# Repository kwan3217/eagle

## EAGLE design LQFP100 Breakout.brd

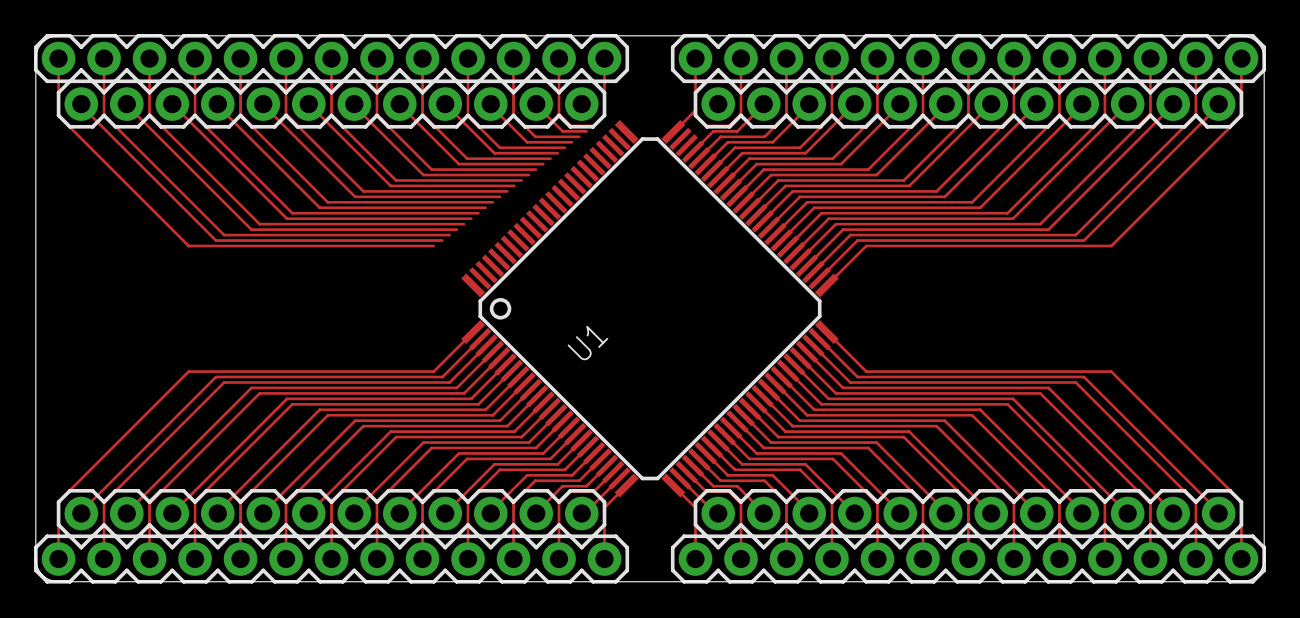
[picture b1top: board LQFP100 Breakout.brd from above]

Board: 2 copper layers, 68.6 x 30.5 mm, 9 parts (0 on the bottom side), 100 nets.

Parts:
JP1, JP2, JP3, JP4: M13; 1X13
JP5, JP6, JP7, JP8: M12PTH; 1X12
U1: LPC2368; LQFP100

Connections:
unnamed: JP1.1, U1.1
unnamed: JP5.1, U1.2
unnamed: JP1.2, U1.3
unnamed: JP5.2, U1.4
unnamed: JP1.3, U1.5
unnamed: JP5.3, U1.6
unnamed: JP1.4, U1.7
unnamed: JP5.4, U1.8
unnamed: JP1.5, U1.9
unnamed: JP5.5, U1.10
unnamed: JP1.6, U1.11
unnamed: JP5.6, U1.12
unnamed: JP1.7, U1.13
unnamed: JP5.7, U1.14
unnamed: JP1.8, U1.15
unnamed: JP5.8, U1.16
unnamed: JP1.9, U1.17
unnamed: JP5.9, U1.18
unnamed: JP1.10, U1.19
unnamed: JP5.10, U1.20
unnamed: JP1.11, U1.21
unnamed: JP5.11, U1.22
unnamed: JP1.12, U1.23
unnamed: JP5.12, U1.24
unnamed: JP1.13, U1.25
unnamed: JP2.13, U1.26
unnamed: JP6.12, U1.27
unnamed: JP2.12, U1.28
unnamed: JP6.11, U1.29
unnamed: JP2.11, U1.30
unnamed: JP6.10, U1.31
unnamed: JP2.10, U1.32
unnamed: JP6.9, U1.33
unnamed: JP2.9, U1.34
unnamed: JP6.8, U1.35
unnamed: JP2.8, U1.36
unnamed: JP6.7, U1.37
unnamed: JP2.7, U1.38
unnamed: JP6.6, U1.39
unnamed: JP2.6, U1.40
unnamed: JP6.5, U1.41
unnamed: JP2.5, U1.42
unnamed: JP6.4, U1.43
unnamed: JP2.4, U1.44
unnamed: JP6.3, U1.45
unnamed: JP2.3, U1.46
unnamed: JP6.2, U1.47
unnamed: JP2.2, U1.48
unnamed: JP6.1, U1.49
unnamed: JP2.1, U1.50
unnamed: JP4.13, U1.51
unnamed: JP7.12, U1.52
unnamed: JP4.12, U1.53
unnamed: JP7.11, U1.54
unnamed: JP4.11, U1.55
unnamed: JP7.10, U1.56
unnamed: JP4.10, U1.57
unnamed: JP7.9, U1.58
unnamed: JP4.9, U1.59
unnamed: JP7.8, U1.60
unnamed: JP4.8, U1.61
unnamed: JP7.7, U1.62
unnamed: JP4.7, U1.63
unnamed: JP7.6, U1.64
unnamed: JP4.6, U1.65
unnamed: JP7.5, U1.66
unnamed: JP4.5, U1.67
unnamed: JP7.4, U1.68
unnamed: JP4.4, U1.69
unnamed: JP7.3, U1.70
unnamed: JP4.3, U1.71
unnamed: JP7.2, U1.72
unnamed: JP4.2, U1.100
unnamed: JP7.1, U1.99
unnamed: JP4.1, U1.98
unnamed: JP3.13, U1.83
unnamed: JP8.12, U1.96
unnamed: JP3.12, U1.95
unnamed: JP8.11, U1.94
unnamed: JP3.11, U1.93
unnamed: JP8.10, U1.92
unnamed: JP3.10, U1.73
unnamed: JP8.9, U1.74
unnamed: JP3.9, U1.75
unnamed: JP8.8, U1.76
unnamed: JP3.8, U1.77
unnamed: JP8.7, U1.78
unnamed: JP3.7, U1.79
unnamed: JP8.6, U1.80
unnamed: JP3.6, U1.81
unnamed: JP8.5, U1.82
unnamed: JP3.5, U1.97
unnamed: JP8.4, U1.84
unnamed: JP3.4, U1.85
unnamed: JP8.3, U1.86
unnamed: JP3.3, U1.87
unnamed: JP8.2, U1.88
unnamed: JP3.2, U1.89
unnamed: JP8.1, U1.90
unnamed: JP3.1, U1.91

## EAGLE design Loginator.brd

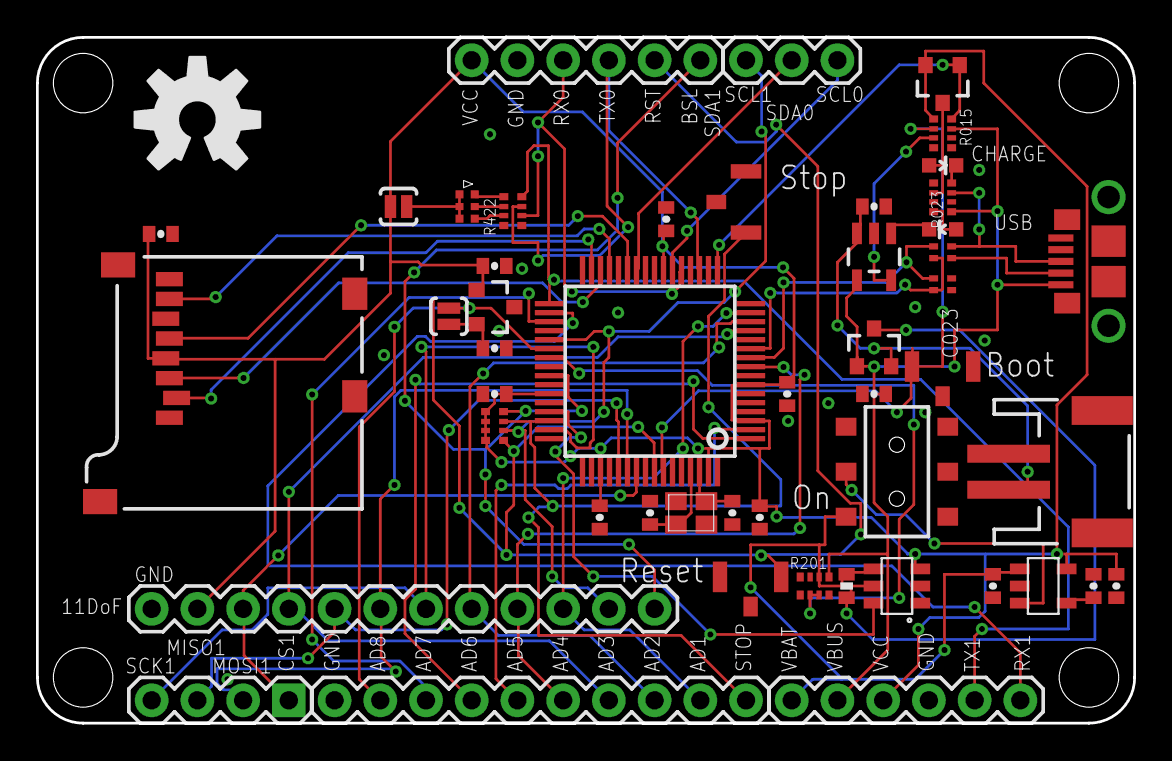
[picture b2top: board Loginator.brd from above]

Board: 2 copper layers, 61.0 x 38.1 mm, 55 parts (1 on the bottom side), 54 nets.

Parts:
C023: 22pF; CKCM25
C201, C301, C302, C438: 4.7uF; 0402-CAP
C203, C407, C423, C432, C443, C451, C463, C701: 100nF; 0402-CAP
C204: 1uF; 0402-CAP
C461, C462: 18pF; 0402-CAP
D050: YELLOW; LED-0603
D301: BLUE; LED-0603
D302: DCC; SOT-23-3
D401: SMLP36
J001: USB_MICROB_JSTGCT; USB_MICROB_3075
J002: M01PTH; 1X03
J301: JST 2mm; JST-2-SMD
J401, J404: M06; 1X06
J402: M04; 1X04
J403: M10; 1X10
J406: 11DoF; 1X12
JP1, JP2, JP3, JP4: STAND-OFF
Q050: PMOS; SOT23-3
R015, R401: 10k; CRA04
R023: 33; CRA02
R053: 1.5k; CRA04
R201: 100k; CRA04
R203: 0.047; 0402-RES
R422: 150; CRA04
S010, S420, S457: SPST; B3U-1100P
S201: AYZ0202
S401, S438: SOLDERJUMPERNO; SJ_2S-NO
U201: 5319; SOT-23-5
U202: 4173; SOT-23-6
U301: 73831; SOT23-5
U401: LPC2148; SQFP-S-10X10-64
U402: 1525; SOT-23-3
U701: MICROSD-SOCKET; MICROSD-SOCKET-PP
U$1: KWAN_CIRCLE
U$2: OSHW-LOGO-L
Y401: 12MHz; CRYSTAL_SMD_2MM_2_5MM

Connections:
AD1: J403.9, J406.3, U401.15
AD2: J403.8, J406.5, U401.14
AD3: J403.7, J406.9, U401.13
AD4: J403.6, J406.4, U401.9
AD5: J403.5, U401.2
AD6: J403.4, U401.1
AD7: J403.3, U401.35
ADREF+: C438.1, S438.1, U402.2
ADREF-: J403.2, S438.2, U401.38
BATLVL: R201.2, R201.3, U401.39
CONN_D+: J001.3, R023.2, R053.7
CONN_D-: J001.2, R023.1
CS0: U401.31, U701.2
CS1: J402.1, J406.10, U401.55
CURRENT: U202.6, U401.45
DB: D401.3, R422.6
DG: D401.5, R422.7
DR: D401.1, R422.5
EN: S201.2, U201.3
GND: C023.3, C023.4, C201.2, C203.2, C204.2, C301.2, C302.2, C407.2, C423.2, C432.2, C438.2, C443.2, C451.2, C461.1, C462.1, C463.2, C701.2, J001.5, J001.P$1, J001.P$2, J001.P$3, J001.P$4, J001.P$8, J001.P$10, J301.1, J401.5, J403.1, J404.4, J406.12, R015.6, R053.1, R201.1, R201.4, R201.7, R201.8, S010.P$2, S010.P$3, S201.3, S420.P$1, S420.P$3, S457.P$1, S457.P$3, U201.2, U202.1, U202.2, U301.2, U401.6, U401.18, U401.25, U401.42, U401.50, U401.59, U402.3, U701.6, U701.CD2, U701.GND1, U701.GND3, Y401.2, Y401.4
MISO0: U401.29, U701.7
MISO1: J402.3, J406.8, U401.53
MOSI0: U401.30, U701.3
MOSI1: J402.2, J406.7, U401.54
unnamed: D301.A, R053.4
unnamed: R015.3, U301.5
unnamed: D301.C, U301.1
unnamed: D050.A, Q050.3, R053.2
unnamed: D050.C, R053.8
unnamed: C203.1, U201.4
RGB_Q: D401.2, D401.4, D401.6, S401.1
RST: J401.2, R401.5, S457.P$2, U401.57
RX0/PWMG: J401.4, R422.2, U401.21
RX1: J404.6, U401.34
SCK0: U401.27, U701.5
SCK1: J402.4, J406.6, U401.47
SCL0: J002.1, U401.22
SCL1: J002.3, J406.2, R401.6, U401.37
SDA0: J002.2, U401.26
SDA1/BSL: J401.1, J406.1, R401.8, U401.41
STOP: J403.10, R401.7, S420.P$2, U401.46
TX0/PWMB: J401.3, R422.3, U401.19
TX1/PWMR: J404.5, R422.4, U401.33
USBD+: C023.1, R023.3, U401.10
USBD-: C023.2, R023.4, U401.11
USB_ON: R015.2, S010.P$1, U401.58
USB_SOFTCONNECT: Q050.1, R015.8, U401.17
VBUS: C302.1, D302.1, J001.1, J404.2, R015.7, R053.5, R201.5, U301.4
VCC: C201.1, C407.1, C423.1, C432.1, C443.1, C451.1, C463.1, C701.1, J401.6, J404.3, J406.11, Q050.2, R015.1, R401.1, R401.2, R401.3, R401.4, S401.2, U201.5, U202.3, U401.3, U401.7, U401.23, U401.43, U401.49, U401.51, U401.63, U402.1, U701.4
VIN+: D302.3, R203.1, U202.5
VIN-: C204.1, J404.1, R201.6, R203.2, S201.1, U201.1, U202.4
VLIPO: C301.1, D302.2, J301.2, U301.3
XTAL1: C462.2, U401.62, Y401.1
XTAL2: C461.2, U401.61, Y401.3

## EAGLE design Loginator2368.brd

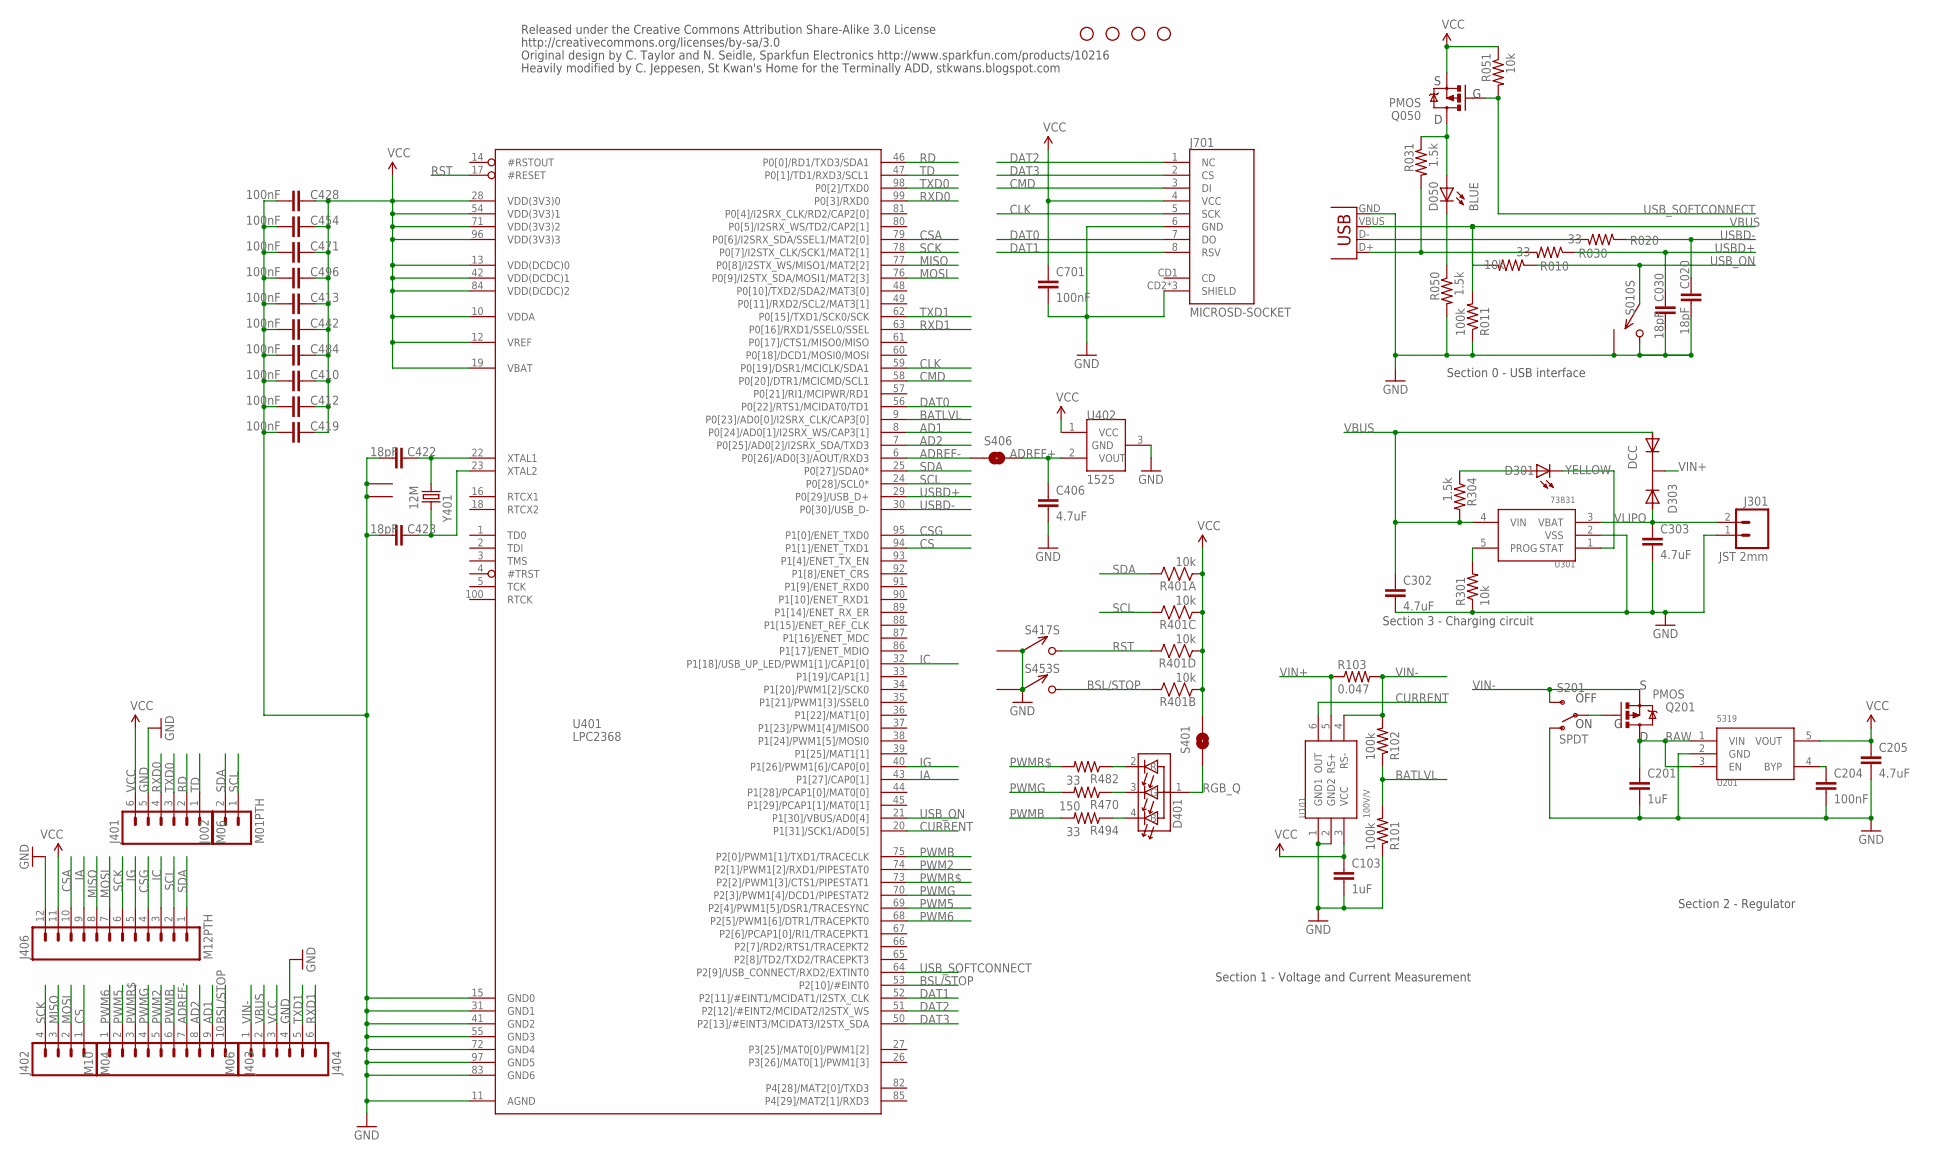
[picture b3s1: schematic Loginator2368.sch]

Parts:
C020, C030, C422, C423: 18pF; 0402-CAP; DIGIKEY 445-1238-1-ND
C103, C201: 1uF; 0402-CAP; DIGIKEY 445-1415-1-ND
C204, C410, C412, C413, C419, C428, C442, C454, C471, C484, C496, C701: 100nF; 0402-CAP; DIGIKEY 445-1268-1-ND
C205, C302, C303, C406: 4.7uF; 0402-CAP; DIGIKEY 445-7395-1-ND
D050: BLUE; LED-0603; DIGIKEY 754-1434-1-ND
D301: YELLOW; LED-0603; DIGIKEY 754-1354-1-ND
D303: DCC; SOT-23-3; DIGIKEY 568-6500-1-ND
D401: RGB; HSMF-C118; DIGIKEY 516-1778-1-ND
J001: USBSMD; USB-MINIB; DIGIKEY 670-1190-1-ND
J002: M01PTH; 1X02; DIGIKEY $NOPART
J301: JST 2mm; JST-2-SMD; DIGIKEY 455-1749-1-ND
J401, J404: M06; 1X06; DIGIKEY $NOPART
J402: M04; 1X04; DIGIKEY $NOPART
J403: M10; 1X10; DIGIKEY $NOPART
J406: M12PTH; 1X12; DIGIKEY $NOPART
J701: MICROSD-SOCKET; MICROSD-SOCKET-PP; DIGIKEY 101-00581-59-1-ND
JP1, JP2, JP3, JP4: STAND-OFF; DIGIKEY $NOPART
Q050, Q201: PMOS; SOT23-3; DIGIKEY NTR1P02T1GOSCT-ND
R010, R051, R301: 10k; 0402-RES; DIGIKEY P10.0KLCT-ND
R011, R101, R102: 100k; 0402-RES; DIGIKEY P100KLCT-ND
R020, R030, R482, R494: 33; 0402-RES; DIGIKEY P33.0LCT-ND
R031, R050, R304: 1.5k; 0402-RES; DIGIKEY P1.50KLCT-ND
R103: 0.047; 0402-RES; DIGIKEY P.047ATCT-ND
R401: 10k; CRA04; DIGIKEY CRA4S810KCT-ND
R470: 150; 0402-RES; DIGIKEY P150LCT-ND
S010, S417, S453: SPST; B3U-1100P; DIGIKEY SW1021CT-ND
S201: SPDT; AYZ0202; DIGIKEY 401-2013-1-ND
S401, S406: SOLDERJUMPERNO; SJ_2S-NO; DIGIKEY $NOPART
U101: 100V/V; SOT-23-6; DIGIKEY MAX4173HEUT+TCT-ND
U201: 5319; SOT-23-5; DIGIKEY 576-1910-1-ND
U301: 73831; SOT-23-5; DIGIKEY MCP73831T-2ACI/OTCT-ND
U401: LPC2368; LQFP100; DIGIKEY 568-3997-ND
U402: 1525; SOT-23-3; DIGIKEY MCP1525T-I/TTCT-ND
Y401: 12M; CRYSTAL_SMD; DIGIKEY 887-1316-1-ND

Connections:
AD1: J403.9, U401.8 (P0[24]/AD0[1]/I2SRX_WS/CAP3[1])
AD2: J403.8, U401.7 (P0[25]/AD0[2]/I2SRX_SDA/TXD3)
ADREF+: C406.1, S406.1, U402.2 (VOUT)
ADREF-: J403.7, S406.2, U401.6 (P0[26]/AD0[3]/AOUT/RXD3)
BATLVL: R101.2, R102.1, U401.9 (P0[23]/AD0[0]/I2SRX_CLK/CAP3[0])
BSL/STOP: J403.10, R401.7 (2), S453.P$2 (2), U401.53 (P2[10]/#EINT0)
CLK: J701.5 (SCK), U401.59 (P0[19]/DSR1/MCICLK/SDA1)
CMD: J701.3 (DI), U401.58 (P0[20]/DTR1/MCICMD/SCL1)
CONN_D+: J001.D+, R030.2, R031.2
CONN_D-: J001.D-, R020.2
CS: J402.1, U401.94 (P1[1]/ENET_TXD1)
CSA: J406.10, U401.79 (P0[6]/I2SRX_SDA/SSEL1/MAT2[0])
CSG: J406.4, U401.95 (P1[0]/ENET_TXD0)
CURRENT: U101.6 (OUT), U401.20 (P1[31]/SCK1/AD0[5])
DAT0: J701.7 (DO), U401.56 (P0[22]/RTS1/MCIDAT0/TD1)
DAT1: J701.8 (RSV), U401.52 (P2[11]/#EINT1/MCIDAT1/I2STX_CLK)
DAT2: J701.1 (NC), U401.51 (P2[12]/#EINT2/MCIDAT2/I2STX_WS)
DAT3: J701.2 (CS), U401.50 (P2[13]/#EINT3/MCIDAT3/I2STX_SDA)
DB: D401.4 (B), R494.1
DG: D401.2 (R), R482.1
DR: D401.3 (G), R470.1
GND: C020.2, C030.2, C103.2, C201.2, C204.2, C205.2, C302.2, C303.2, C406.2, C410.2, C412.2, C413.2, C419.2, C422.1, C423.1, C428.2, C442.2, C454.2, C471.2, C484.2, C496.2, C701.2, J001.GND, J301.1, J401.5, J404.4, J406.12, J701.6 (GND), J701.CD2 (SHIELD), J701.GND1 (SHIELD), J701.GND3 (SHIELD), R011.1, R050.2, R101.1, R301.1, S010.P$2 (2), S010.P$3 (1), S201.1 (O), S417.P$1 (1), S417.P$3 (1), S453.P$1 (1), S453.P$3 (1), U101.1 (GND1), U101.2 (GND2), U201.2 (GND), U301.2 (VSS), U401.11 (AGND), U401.15 (GND0), U401.31 (GND1), U401.41 (GND2), U401.55 (GND3), U401.72 (GND4), U401.83 (GND6), U401.97 (GND5), U402.3 (GND), Y401.2 (1), Y401.4 (1)
IA: J406.9, U401.43 (P1[27]/CAP0[1])
IC: J406.3, U401.32 (P1[18]/USB_UP_LED/PWM1[1]/CAP1[0])
IG: J406.5, U401.40 (P1[26]/PWM1[6]/CAP0[0])
MISO: J402.3, J406.8, U401.77 (P0[8]/I2STX_WS/MISO1/MAT2[2])
MOSI: J402.2, J406.7, U401.76 (P0[9]/I2STX_SDA/MOSI1/MAT2[3])
unnamed: D301.A, R304.1
unnamed: R301.2, U301.5 (PROG)
unnamed: D301.C, U301.1 (STAT)
unnamed: D050.A, Q050.3 (D), R031.1
unnamed: D050.C, R050.1
unnamed: Q201.1 (G), S201.2
unnamed: C204.1, U201.4 (BYP)
PWM2: J403.5, U401.74 (P2[1]/PWM1[2]/RXD1/PIPESTAT0)
PWM5: J403.2, U401.69 (P2[4]/PWM1[5]/DSR1/TRACESYNC)
PWM6: J403.1, U401.68 (P2[5]/PWM1[6]/DTR1/TRACEPKT0)
PWMB: J403.6, R494.2, U401.75 (P2[0]/PWM1[1]/TXD1/TRACECLK)
PWMG: J403.4, R470.2, U401.70 (P2[3]/PWM1[4]/DCD1/PIPESTAT2)
PWMR$: J403.3, R482.2, U401.73 (P2[2]/PWM1[3]/CTS1/PIPESTAT1)
RAW: C201.1, Q201.3 (D), U201.1 (VIN), U201.3 (EN)
RD: J401.2, U401.46 (P0[0]/RD1/TXD3/SDA1)
RGB_Q: D401.1 (A), S401.1
RST: R401.5 (2), S417.P$2 (2), U401.17 (#RESET)
RXD0: J401.4, U401.99 (P0[3]/RXD0)
RXD1: J404.6, U401.63 (P0[16]/RXD1/SSEL0/SSEL)
SCK: J402.4, J406.6, U401.78 (P0[7]/I2STX_CLK/SCK1/MAT2[1])
SCL: J002.1, J406.2, R401.6 (2), U401.24 (P0[28]/SCL0*)
SDA: J002.2, J406.1, R401.8 (2), U401.25 (P0[27]/SDA0*)
TD: J401.1, U401.47 (P0[1]/TD1/RXD3/SCL1)
TXD0: J401.3, U401.98 (P0[2]/TXD0)
TXD1: J404.5, U401.62 (P0[15]/TXD1/SCK0/SCK)
USBD+: C030.1, R030.1, U401.29 (P0[29]/USB_D+)
USBD-: C020.1, R020.1, U401.30 (P0[30]/USB_D-)
USB_ON: R010.1, S010.P$1 (1), U401.21 (P1[30]/VBUS/AD0[4])
USB_SOFTCONNECT: Q050.1 (G), R051.2, U401.64 (P2[9]/USB_CONNECT/RXD2/EXTINT0)
VBUS: C302.1, D303.1 (A1), J001.VBUS, J404.2, R010.2, R011.2, R304.2, U301.4 (VIN)
VCC: C103.1, C205.1, C410.1, C412.1, C413.1, C419.1, C428.1, C442.1, C454.1, C471.1, C484.1, C496.1, C701.1, J401.6, J404.3, J406.11, J701.4 (VCC), Q050.2 (S), R051.1, R401.1, R401.2 (1), R401.3 (1), R401.4 (1), S401.2, U101.3 (VCC), U201.5 (VOUT), U401.10 (VDDA), U401.12 (VREF), U401.13 (VDD(DCDC)0), U401.19 (VBAT), U401.28 (VDD(3V3)0), U401.42 (VDD(DCDC)1), U401.54 (VDD(3V3)1), U401.71 (VDD(3V3)2), U401.84 (VDD(DCDC)2), U401.96 (VDD(3V3)3), U402.1 (VCC)
VIN+: D303.3 (K), R103.1, U101.5 (RS+)
VIN-: J404.1, Q201.2 (S), R102.2, R103.2, S201.3 (S), U101.4 (RS-)
VLIPO: C303.1, D303.2 (A2), J301.2, U301.3 (VBAT)
XTAL1: C422.2, U401.22 (XTAL1), Y401.3 (2)
XTAL2: C423.2, U401.23 (XTAL2), Y401.1

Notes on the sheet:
Section 2 - Regulator
Section 3 - Charging circuit
Section 0 - USB interface
Released under the Creative Commons Attribution Share-Alike 3.0 License
http://creativecommons.org/licenses/by-sa/3.0
Original design by C. Taylor and N. Seidle, Sparkfun Electronics http://www.sparkfun.com/products/10216
Heavily modified by C. Jeppesen, St Kwan's Home for the Terminally ADD, stkwans.blogspot.com
Section 1 - Voltage and Current Measurement
OFF

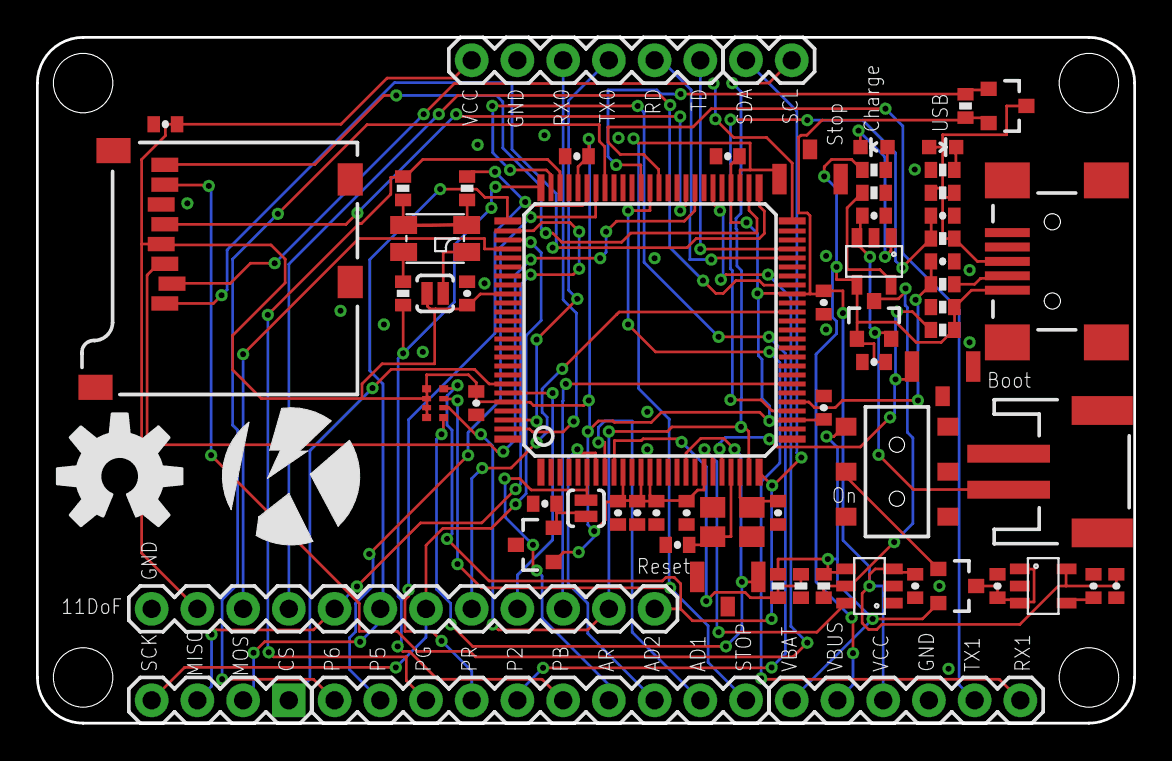
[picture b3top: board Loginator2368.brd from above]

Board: 2 copper layers, 61.0 x 38.1 mm, 71 parts (0 on the bottom side), 63 nets.

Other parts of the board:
U$1: KWAN_CIRCLE
U$2: OSHW-LOGO-L

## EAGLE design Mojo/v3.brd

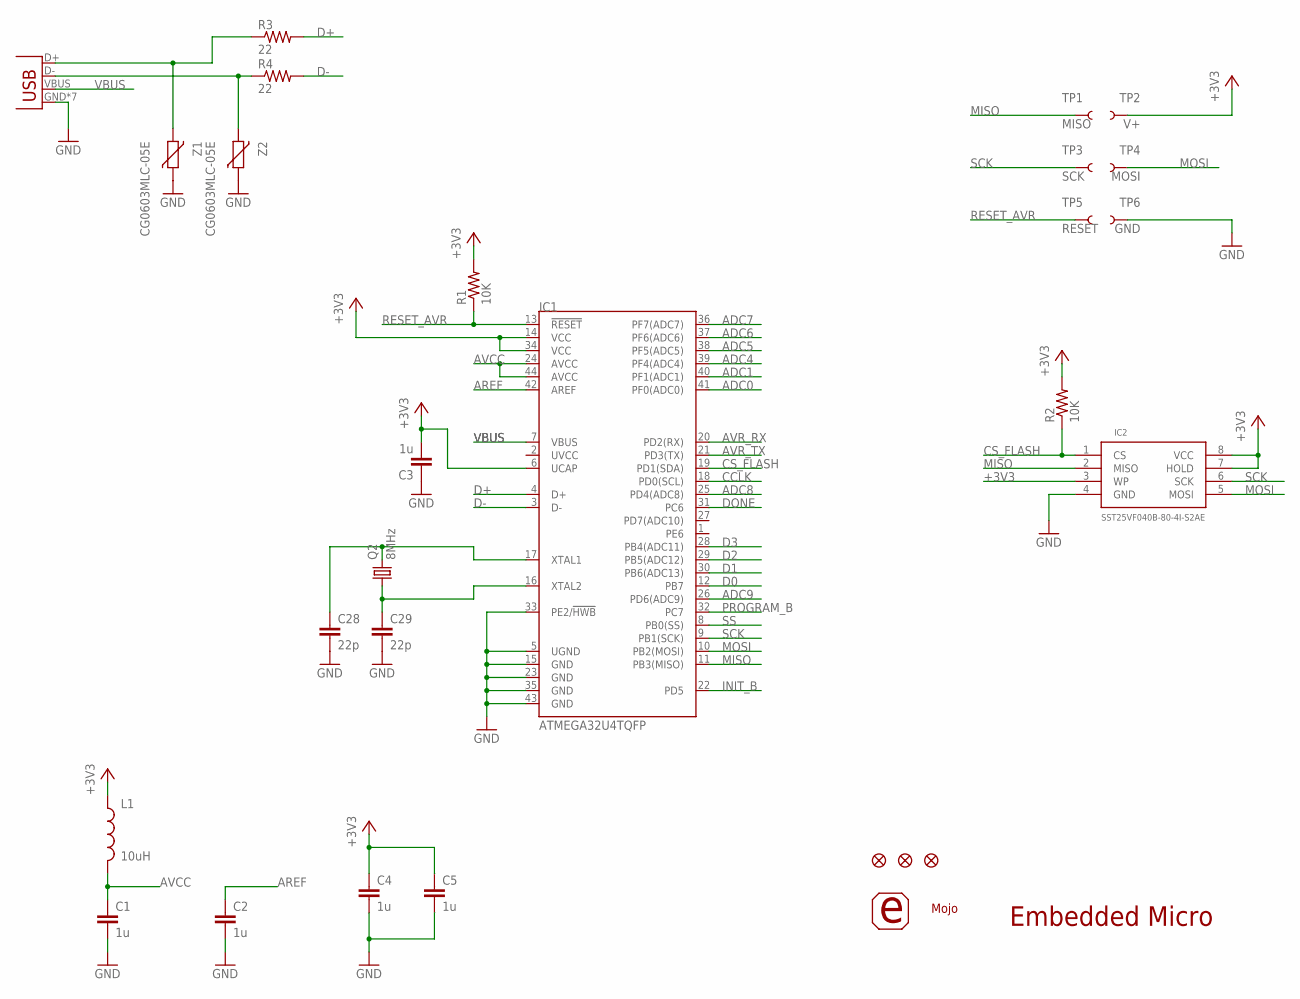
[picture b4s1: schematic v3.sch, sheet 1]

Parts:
C1, C2, C3, C4, C5: 1u; C0603K
C28, C29: 22p; C0603K
IC1: ATMEGA32U4TQFP; SPARKFUN-DIGITALIC_TQFP44
IC2: SST25VF040B-80-4I-S2AE; SO08-EIAJ
JP3, JP4, JP5: FIDUCIAL1X2; FIDUCIAL-1X2
L1: 10uH; 0603
Q2: 8MHz; ABM2
R1, R2: 10K; R0603
R3, R4: 22; R0603
TP1: MISO; PAD.03X.05
TP2: V+; PAD.03X.05
TP3: SCK; PAD.03X.05
TP4: MOSI; PAD.03X.05
TP5: RESET; PAD.03X.05
TP6: GND; PAD.03X.05
U$1: LOGO(SMALL)SMALL; LOGO
U$2: MOJO_LOGOV3; MOJO_LOGO_V3
X1: USB-MICROB
Z1, Z2: CG0603MLC-05E; CT/CN0603

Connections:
+3V3: C3.2, C4.1, C5.1, IC1.6 (UCAP), IC1.14 (VCC), IC1.34 (VCC), IC2.3 (WP), IC2.7 (HOLD), IC2.8 (VCC), L1.1, R1.2, R2.2, TP2.P$1; also elsewhere on the board
ADC0: IC1.41 (PF0(ADC0)); also elsewhere on the board
ADC1: IC1.40 (PF1(ADC1)); also elsewhere on the board
ADC4: IC1.39 (PF4(ADC4)); also elsewhere on the board
ADC5: IC1.38 (PF5(ADC5)); also elsewhere on the board
ADC6: IC1.37 (PF6(ADC6)); also elsewhere on the board
ADC7: IC1.36 (PF7(ADC7)); also elsewhere on the board
ADC8: IC1.25 (PD4(ADC8)); also elsewhere on the board
ADC9: IC1.26 (PD6(ADC9)); also elsewhere on the board
AREF: C2.1, IC1.42 (AREF); also elsewhere on the board
AVCC: C1.1, IC1.24 (AVCC), IC1.44 (AVCC), L1.2
AVR_RX: IC1.20 (PD2(RX)); also elsewhere on the board
AVR_TX: IC1.21 (PD3(TX)); also elsewhere on the board
CCLK: IC1.18 (PD0(SCL)); also elsewhere on the board
CS_FLASH: IC1.19 (PD1(SDA)), IC2.1 (CS), R2.1
D0: IC1.12 (PB7); also elsewhere on the board
D1: IC1.30 (PB6(ADC13)); also elsewhere on the board
D2: IC1.29 (PB5(ADC12)); also elsewhere on the board
D3: IC1.28 (PB4(ADC11)); also elsewhere on the board
D+: IC1.4 (D+), R3.2
D-: IC1.3 (D-), R4.2
DONE: IC1.31 (PC6); also elsewhere on the board
GND: C1.2, C2.2, C3.1, C4.2, C5.2, C28.2, C29.2, IC1.5 (UGND), IC1.15 (GND), IC1.23 (GND), IC1.33 (PE2/!HWB), IC1.35 (GND), IC1.43 (GND), IC2.4 (GND), TP6.P$1, X1.GND, X1.P1 (GND), X1.P2 (GND), X1.P3 (GND), X1.P4 (GND), X1.P5 (GND), X1.P6 (GND), Z1.1, Z2.1; also elsewhere on the board
INIT_B: IC1.22 (PD5); also elsewhere on the board
MISO: IC1.11 (PB3(MISO)), IC2.2 (MISO), TP1.P$1; also elsewhere on the board
MOSI: IC1.10 (PB2(MOSI)), IC2.5 (MOSI), TP4.P$1; also elsewhere on the board
unnamed: R3.1, X1.D+, Z1.2
unnamed: R4.1, X1.D-, Z2.2
unnamed: C28.1, IC1.17 (XTAL1), Q2.P$2 (2)
unnamed: C29.1, IC1.16 (XTAL2), Q2.P$1 (1)
PROGRAM_B: IC1.32 (PC7); also elsewhere on the board
RESET_AVR: IC1.13 (!RESET), R1.1, TP5.P$1
SCK: IC1.9 (PB1(SCK)), IC2.6 (SCK), TP3.P$1; also elsewhere on the board
SS: IC1.8 (PB0(SS)); also elsewhere on the board
VBUS: IC1.7 (VBUS), X1.VBUS; also elsewhere on the board

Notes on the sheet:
Embedded Micro

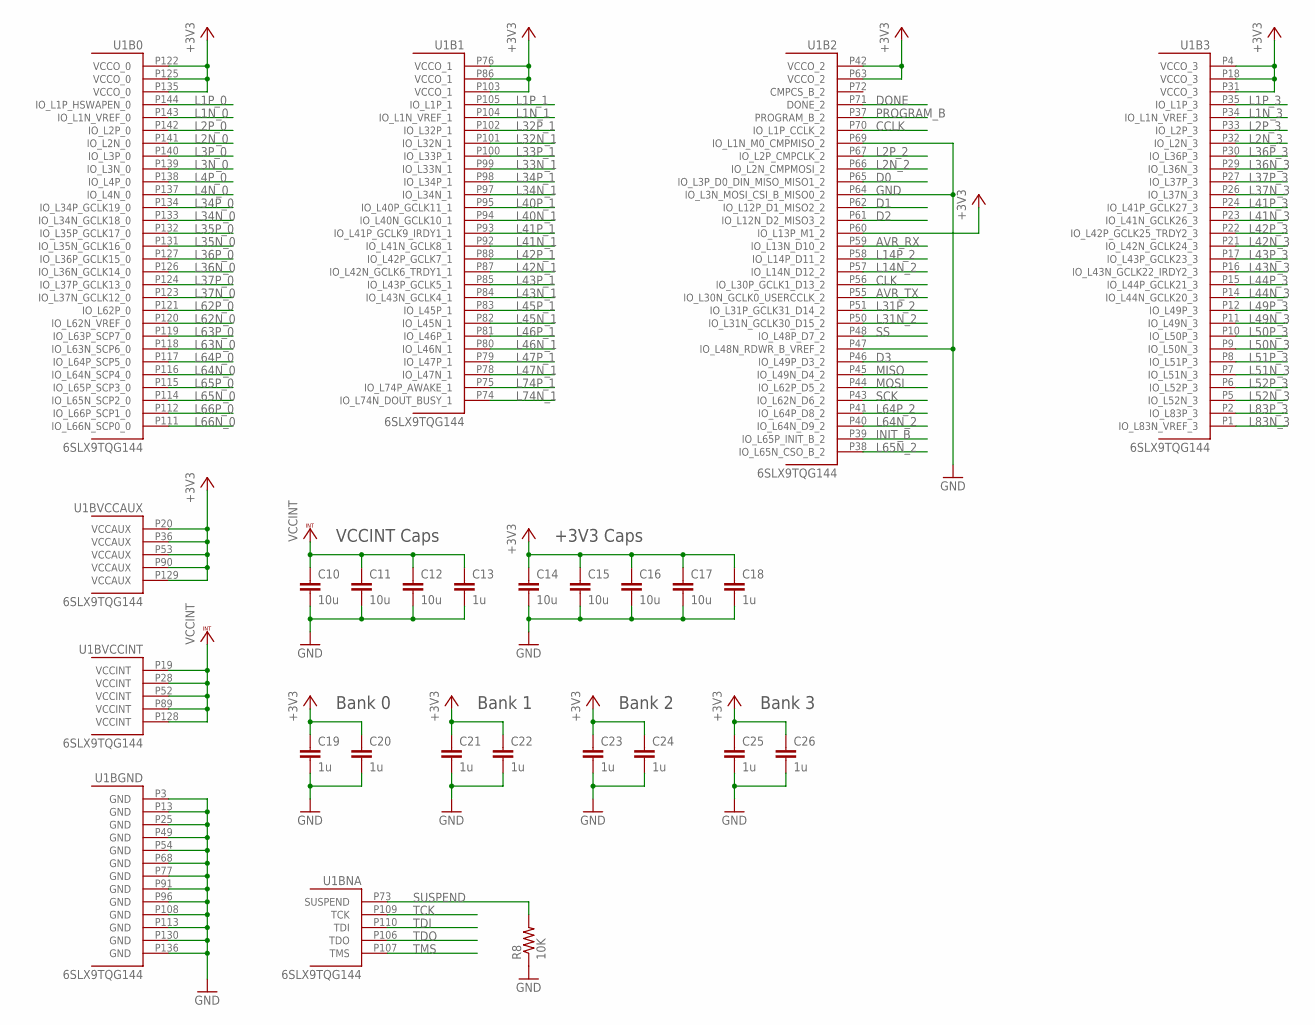
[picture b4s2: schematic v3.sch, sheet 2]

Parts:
C10, C11, C12, C14, C15, C16, C17: 10u; C0603K
C13, C18, C19, C20, C21, C22, C23, C24, C25, C26: 1u; C0603K
R8: 10K; R0603
U1: 6SLX9TQG144; TQ144

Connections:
+3V3: C14.1, C15.1, C16.1, C17.1, C18.1, C19.1, C20.1, C21.1, C22.1, C23.1, C24.1, C25.1, C26.1, U1.P4 (VCCO_3), U1.P18 (VCCO_3), U1.P20 (VCCAUX), U1.P31 (VCCO_3), U1.P36 (VCCAUX), U1.P42 (VCCO_2), U1.P53 (VCCAUX), U1.P60 (IO_L13P_M1_2), U1.P63 (VCCO_2), U1.P76 (VCCO_1), U1.P86 (VCCO_1), U1.P90 (VCCAUX), U1.P103 (VCCO_1), U1.P122 (VCCO_0), U1.P125 (VCCO_0), U1.P129 (VCCAUX), U1.P135 (VCCO_0); also elsewhere on the board
AVR_RX: U1.P59 (IO_L13N_D10_2); also elsewhere on the board
AVR_TX: U1.P55 (IO_L30N_GCLK0_USERCCLK_2); also elsewhere on the board
CCLK: U1.P70 (IO_L1P_CCLK_2); also elsewhere on the board
CLK: U1.P56 (IO_L30P_GCLK1_D13_2); also elsewhere on the board
D0: U1.P65 (IO_L3P_D0_DIN_MISO_MISO1_2); also elsewhere on the board
D1: U1.P62 (IO_L12P_D1_MISO2_2); also elsewhere on the board
D2: U1.P61 (IO_L12N_D2_MISO3_2); also elsewhere on the board
D3: U1.P46 (IO_L49P_D3_2); also elsewhere on the board
DONE: U1.P71 (DONE_2); also elsewhere on the board
GND: C10.2, C11.2, C12.2, C13.2, C14.2, C15.2, C16.2, C17.2, C18.2, C19.2, C20.2, C21.2, C22.2, C23.2, C24.2, C25.2, C26.2, R8.1, U1.P3 (GND), U1.P13 (GND), U1.P25 (GND), U1.P47 (IO_L48N_RDWR_B_VREF_2), U1.P49 (GND), U1.P54 (GND), U1.P64 (IO_L3N_MOSI_CSI_B_MISO0_2), U1.P68 (GND), U1.P69 (IO_L1N_M0_CMPMISO_2), U1.P77 (GND), U1.P91 (GND), U1.P96 (GND), U1.P108 (GND), U1.P113 (GND), U1.P130 (GND), U1.P136 (GND); also elsewhere on the board
INIT_B: U1.P39 (IO_L65P_INIT_B_2); also elsewhere on the board
L1N_0: U1.P143 (IO_L1N_VREF_0); also elsewhere on the board
L1N_1: U1.P104 (IO_L1N_VREF_1); also elsewhere on the board
L1N_3: U1.P34 (IO_L1N_VREF_3); also elsewhere on the board
L1P_0: U1.P144 (IO_L1P_HSWAPEN_0); also elsewhere on the board
L1P_1: U1.P105 (IO_L1P_1); also elsewhere on the board
L1P_3: U1.P35 (IO_L1P_3); also elsewhere on the board
L2N_0: U1.P141 (IO_L2N_0); also elsewhere on the board
L2N_2: U1.P66 (IO_L2N_CMPMOSI_2); also elsewhere on the board
L2N_3: U1.P32 (IO_L2N_3); also elsewhere on the board
L2P_0: U1.P142 (IO_L2P_0); also elsewhere on the board
L2P_2: U1.P67 (IO_L2P_CMPCLK_2); also elsewhere on the board
L2P_3: U1.P33 (IO_L2P_3); also elsewhere on the board
L3N_0: U1.P139 (IO_L3N_0); also elsewhere on the board
L3P_0: U1.P140 (IO_L3P_0); also elsewhere on the board
L4N_0: U1.P137 (IO_L4N_0); also elsewhere on the board
L4P_0: U1.P138 (IO_L4P_0); also elsewhere on the board
L14N_2: U1.P57 (IO_L14N_D12_2); also elsewhere on the board
L14P_2: U1.P58 (IO_L14P_D11_2); also elsewhere on the board
L31N_2: U1.P50 (IO_L31N_GCLK30_D15_2); also elsewhere on the board
L31P_2: U1.P51 (IO_L31P_GCLK31_D14_2); also elsewhere on the board
L32N_1: U1.P101 (IO_L32N_1); also elsewhere on the board
L32P_1: U1.P102 (IO_L32P_1); also elsewhere on the board
L33N_1: U1.P99 (IO_L33N_1); also elsewhere on the board
L33P_1: U1.P100 (IO_L33P_1); also elsewhere on the board
L34N_0: U1.P133 (IO_L34N_GCLK18_0); also elsewhere on the board
L34N_1: U1.P97 (IO_L34N_1); also elsewhere on the board
L34P_0: U1.P134 (IO_L34P_GCLK19_0); also elsewhere on the board
L34P_1: U1.P98 (IO_L34P_1); also elsewhere on the board
L35N_0: U1.P131 (IO_L35N_GCLK16_0); also elsewhere on the board
L35P_0: U1.P132 (IO_L35P_GCLK17_0); also elsewhere on the board
L36N_0: U1.P126 (IO_L36N_GCLK14_0); also elsewhere on the board
L36N_3: U1.P29 (IO_L36N_3); also elsewhere on the board
L36P_0: U1.P127 (IO_L36P_GCLK15_0); also elsewhere on the board
L36P_3: U1.P30 (IO_L36P_3); also elsewhere on the board
L37N_0: U1.P123 (IO_L37N_GCLK12_0); also elsewhere on the board
L37N_3: U1.P26 (IO_L37N_3); also elsewhere on the board
L37P_0: U1.P124 (IO_L37P_GCLK13_0); also elsewhere on the board
L37P_3: U1.P27 (IO_L37P_3); also elsewhere on the board
L40N_1: U1.P94 (IO_L40N_GCLK10_1); also elsewhere on the board
L40P_1: U1.P95 (IO_L40P_GCLK11_1); also elsewhere on the board
L41N_1: U1.P92 (IO_L41N_GCLK8_1); also elsewhere on the board
L41N_3: U1.P23 (IO_L41N_GCLK26_3); also elsewhere on the board
L41P_1: U1.P93 (IO_L41P_GCLK9_IRDY1_1); also elsewhere on the board
L41P_3: U1.P24 (IO_L41P_GCLK27_3); also elsewhere on the board
L42N_1: U1.P87 (IO_L42N_GCLK6_TRDY1_1); also elsewhere on the board
L42N_3: U1.P21 (IO_L42N_GCLK24_3); also elsewhere on the board
L42P_1: U1.P88 (IO_L42P_GCLK7_1); also elsewhere on the board
L42P_3: U1.P22 (IO_L42P_GCLK25_TRDY2_3); also elsewhere on the board
L43N_1: U1.P84 (IO_L43N_GCLK4_1); also elsewhere on the board
L43N_3: U1.P16 (IO_L43N_GCLK22_IRDY2_3); also elsewhere on the board
L43P_1: U1.P85 (IO_L43P_GCLK5_1); also elsewhere on the board
L43P_3: U1.P17 (IO_L43P_GCLK23_3); also elsewhere on the board
L44N_3: U1.P14 (IO_L44N_GCLK20_3); also elsewhere on the board
L44P_3: U1.P15 (IO_L44P_GCLK21_3); also elsewhere on the board
L45N_1: U1.P82 (IO_L45N_1); also elsewhere on the board
L45P_1: U1.P83 (IO_L45P_1); also elsewhere on the board
L46N_1: U1.P80 (IO_L46N_1); also elsewhere on the board
L46P_1: U1.P81 (IO_L46P_1); also elsewhere on the board
L47N_1: U1.P78 (IO_L47N_1); also elsewhere on the board
L47P_1: U1.P79 (IO_L47P_1); also elsewhere on the board
L49N_3: U1.P11 (IO_L49N_3); also elsewhere on the board
L49P_3: U1.P12 (IO_L49P_3); also elsewhere on the board
L50N_3: U1.P9 (IO_L50N_3); also elsewhere on the board
L50P_3: U1.P10 (IO_L50P_3); also elsewhere on the board
L51N_3: U1.P7 (IO_L51N_3); also elsewhere on the board
L51P_3: U1.P8 (IO_L51P_3); also elsewhere on the board
L52N_3: U1.P5 (IO_L52N_3); also elsewhere on the board
L52P_3: U1.P6 (IO_L52P_3); also elsewhere on the board
L62N_0: U1.P120 (IO_L62N_VREF_0); also elsewhere on the board
L62P_0: U1.P121 (IO_L62P_0); also elsewhere on the board
L63N_0: U1.P118 (IO_L63N_SCP6_0); also elsewhere on the board
L63P_0: U1.P119 (IO_L63P_SCP7_0); also elsewhere on the board
L64N_0: U1.P116 (IO_L64N_SCP4_0); also elsewhere on the board
L64N_2: U1.P40 (IO_L64N_D9_2); also elsewhere on the board
L64P_0: U1.P117 (IO_L64P_SCP5_0); also elsewhere on the board
L64P_2: U1.P41 (IO_L64P_D8_2); also elsewhere on the board
L65N_0: U1.P114 (IO_L65N_SCP2_0); also elsewhere on the board
L65N_2: U1.P38 (IO_L65N_CSO_B_2); also elsewhere on the board
L65P_0: U1.P115 (IO_L65P_SCP3_0); also elsewhere on the board
L66N_0: U1.P111 (IO_L66N_SCP0_0); also elsewhere on the board
L66P_0: U1.P112 (IO_L66P_SCP1_0); also elsewhere on the board
L74N_1: U1.P74 (IO_L74N_DOUT_BUSY_1); also elsewhere on the board
L74P_1: U1.P75 (IO_L74P_AWAKE_1); also elsewhere on the board
L83N_3: U1.P1 (IO_L83N_VREF_3); also elsewhere on the board
L83P_3: U1.P2 (IO_L83P_3); also elsewhere on the board
MISO: U1.P45 (IO_L49N_D4_2); also elsewhere on the board
MOSI: U1.P44 (IO_L62P_D5_2); also elsewhere on the board
PROGRAM_B: U1.P37 (PROGRAM_B_2); also elsewhere on the board
SCK: U1.P43 (IO_L62N_D6_2); also elsewhere on the board
SS: U1.P48 (IO_L48P_D7_2); also elsewhere on the board
SUSPEND: R8.2, U1.P73 (SUSPEND); also elsewhere on the board
TCK: U1.P109 (TCK); also elsewhere on the board
TDI: U1.P110 (TDI); also elsewhere on the board
TDO: U1.P106 (TDO); also elsewhere on the board
TMS: U1.P107 (TMS); also elsewhere on the board
VCCINT: C10.1, C11.1, C12.1, C13.1, U1.P19 (VCCINT), U1.P28 (VCCINT), U1.P52 (VCCINT), U1.P89 (VCCINT), U1.P128 (VCCINT); also elsewhere on the board

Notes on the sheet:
VCCINT Caps
+3V3 Caps
Bank 0
Bank 1
Bank 2
Bank 3

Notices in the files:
parts and their libraries:
SparkFun-Connectors: Licensing: CC v3.0 Share-Alike You are welcome to use this library for commercial purposes.
